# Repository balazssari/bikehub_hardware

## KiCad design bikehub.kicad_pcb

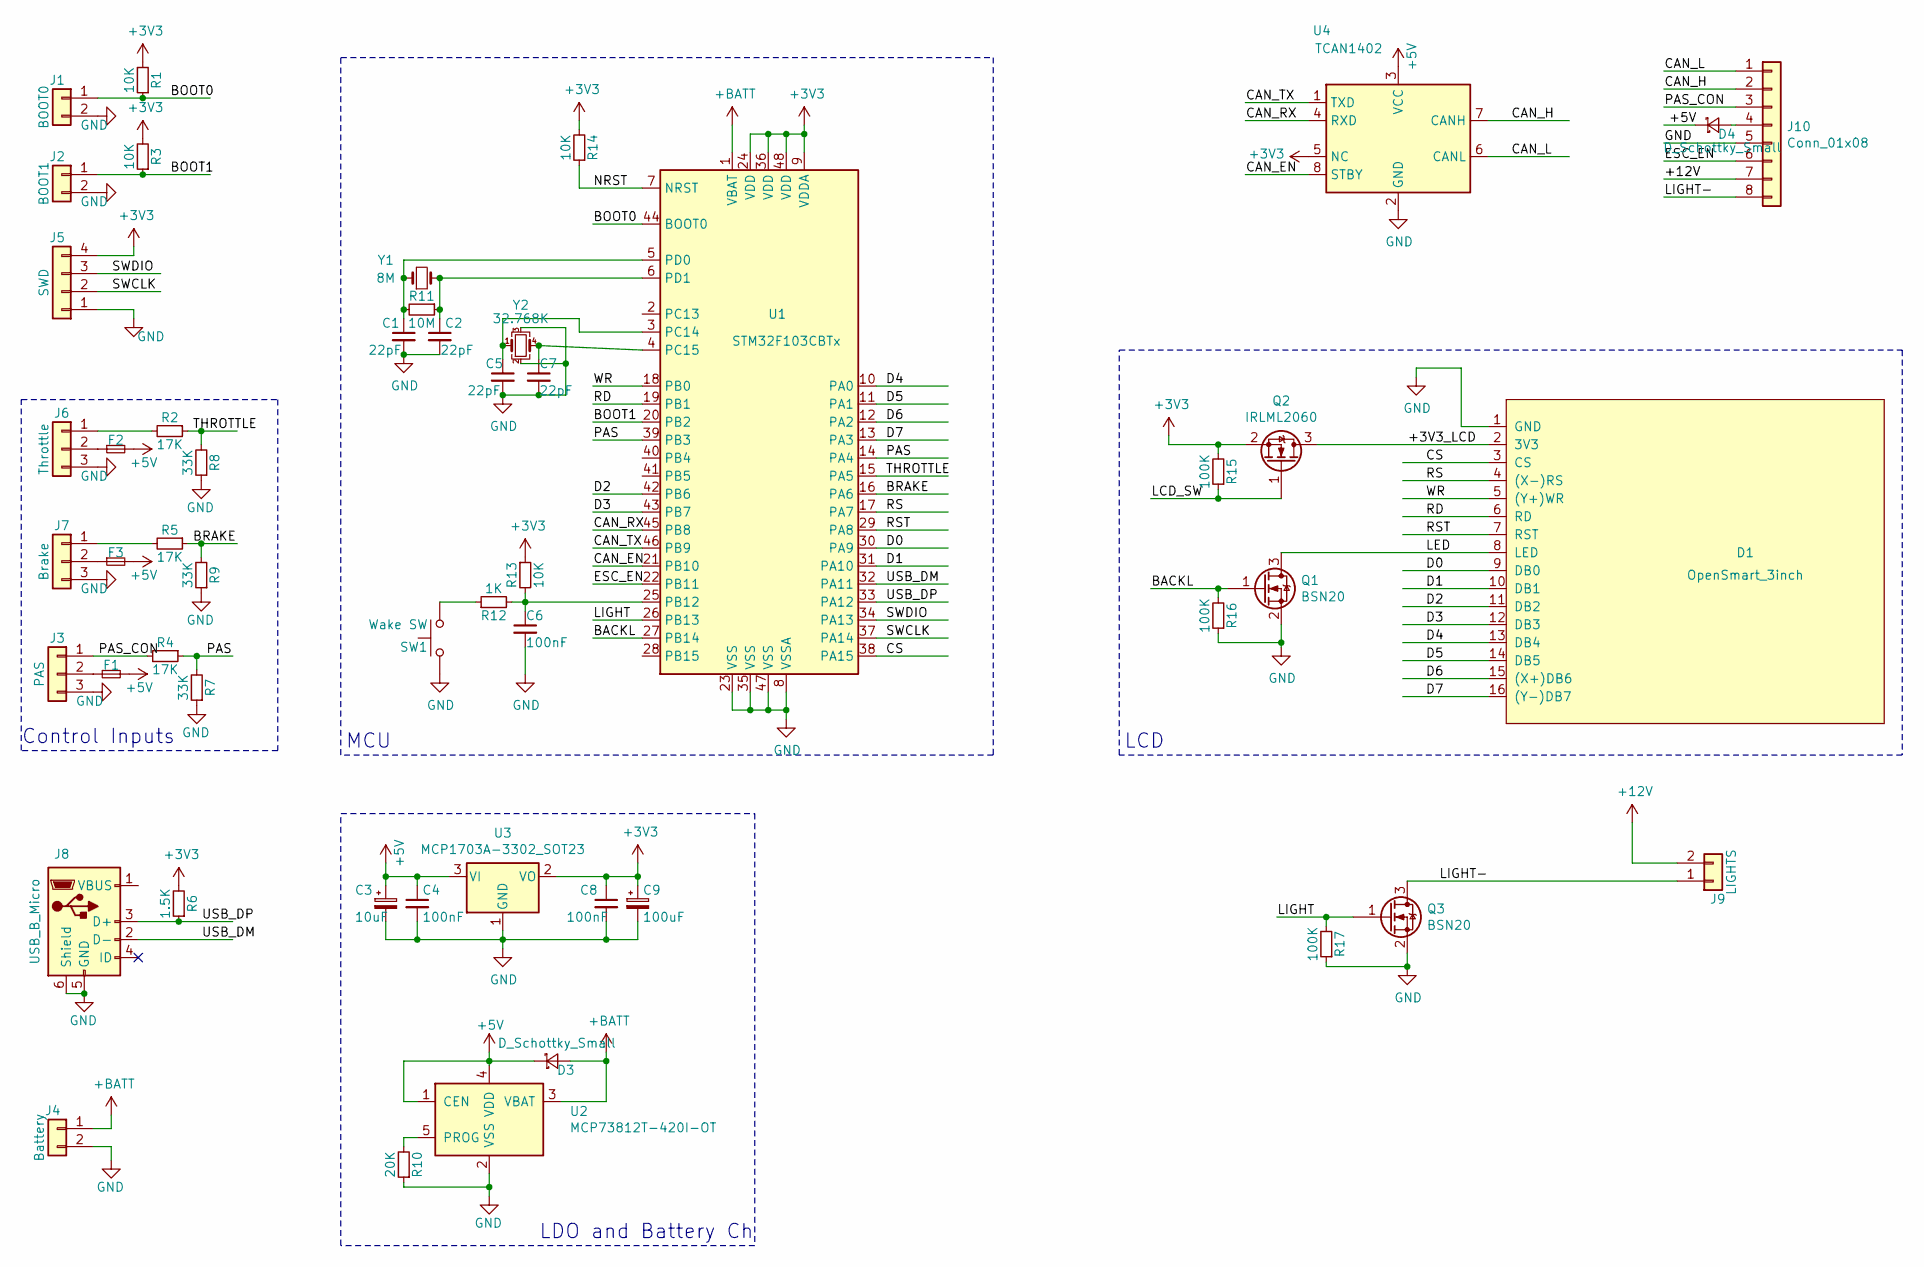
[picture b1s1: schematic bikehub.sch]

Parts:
C1, C2, C5, C7: 22pF; C_0805_2012Metric_Pad1.15x1.40mm_HandSolder
C3: 10uF; C_0805_2012Metric_Pad1.15x1.40mm_HandSolder
C4, C6, C8: 100nF; C_0805_2012Metric_Pad1.15x1.40mm_HandSolder
C9: 100uF; C_0805_2012Metric_Pad1.15x1.40mm_HandSolder
D1: OpenSmart_3inch; PinSocket_1x16_P2.54mm_Vertical_SMD_Pin1Left
D3, D4: D_Schottky_Small; D_SOD-123
F1, F2, F3: Fuse_Small; Fuse_0805_2012Metric
J1: BOOT0; SolderJumper-2_P1.3mm_Open_TrianglePad1.0x1.5mm
J2: BOOT1; SolderJumper-2_P1.3mm_Open_TrianglePad1.0x1.5mm
J3: PAS; JST_XH_S3B-XH-A_1x03_P2.50mm_Horizontal
J4: Battery; PinHeader_1x02_P2.54mm_Vertical
J5: SWD; PinHeader_1x04_P2.54mm_Horizontal
J6: Throttle; JST_XH_S3B-XH-A_1x03_P2.50mm_Horizontal
J7: Brake; JST_XH_S3B-XH-A_1x03_P2.50mm_Horizontal
J8: USB_B_Micro; USB_Micro-B_Molex_47346-0001
J9: LIGHTS; JST_XH_S2B-XH-A_1x02_P2.50mm_Horizontal
J10: Conn_01x08; JST_XH_S8B-XH-A_1x08_P2.50mm_Horizontal
Q1, Q3: BSN20; SOT-23
Q2: IRLML2060; SOT-23
R1, R3, R13, R14: 10K; R_0805_2012Metric_Pad1.15x1.40mm_HandSolder
R2, R4, R5: 17K; R_0805_2012Metric_Pad1.15x1.40mm_HandSolder
R6: 1.5K; R_0805_2012Metric_Pad1.15x1.40mm_HandSolder
R7, R8, R9: 33K; R_0805_2012Metric_Pad1.15x1.40mm_HandSolder
R10: 20K; R_0805_2012Metric_Pad1.15x1.40mm_HandSolder
R11: 10M; R_0805_2012Metric_Pad1.15x1.40mm_HandSolder
R12: 1K; R_0805_2012Metric_Pad1.15x1.40mm_HandSolder
R15, R16, R17: 100K; R_0805_2012Metric_Pad1.15x1.40mm_HandSolder
SW1: Wake SW; SW_SPST_EVQP7A
U1: STM32F103CBTx; LQFP-48_7x7mm_P0.5mm
U2: MCP73812T-420I-OT; SOT-23-5
U3: MCP1703A-3302_SOT23; SOT-23
U4: TCAN1402; SOIC-8_3.9x4.9mm_P1.27mm
Y1: 8M; Crystal_SMD_HC49-SD
Y2: 32.768K; Crystal_SMD_SeikoEpson_MC306-4Pin_8.0x3.2mm

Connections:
+3V3: C8.1, C9.1, J5.4, Q2.2 (S), R1.2, R3.2, R6.2, R13.1, R14.2, R15.2, U1.9 (VDDA), U1.24 (VDD), U1.36 (VDD), U1.48 (VDD), U3.2 (VO), U4.5 (NC)
+5V: C3.1, C4.1, D3.1 (K), D4.1 (K), F1.2, F2.2, F3.2, U2.1 (CEN), U2.4 (VDD), U3.3 (VI), U4.3 (VCC)
+12V: J9.2, J10.7
+BATT: D3.2 (A), J4.1, U1.1 (VBAT), U2.3 (VBAT)
/+3V3_LCD: D1.2 (3V3), Q2.3 (D)
/BACKL: Q1.1 (G), R16.2, U1.27 (PB14)
/BOOT0: J1.1, R1.1, U1.44 (BOOT0)
/BOOT1: J2.1, R3.1, U1.20 (PB2)
/BRAKE: R5.1, R9.2, U1.16 (PA6)
/CAN_EN: U1.21 (PB10), U4.8 (STBY)
/CAN_H: J10.2, U4.7 (CANH)
/CAN_L: J10.1, U4.6 (CANL)
/CAN_RX: U1.45 (PB8), U4.4 (RXD)
/CAN_TX: U1.46 (PB9), U4.1 (TXD)
/CS: D1.3 (CS), U1.38 (PA15)
/D0: D1.9 (DB0), U1.30 (PA9)
/D1: D1.10 (DB1), U1.31 (PA10)
/D2: D1.11 (DB2), U1.42 (PB6)
/D3: D1.12 (DB3), U1.43 (PB7)
/D4: D1.13 (DB4), U1.10 (PA0)
/D5: D1.14 (DB5), U1.11 (PA1)
/D6: D1.15 ((X+)DB6), U1.12 (PA2)
/D7: D1.16 ((Y-)DB7), U1.13 (PA3)
/ESC_EN: J10.6, U1.22 (PB11)
/LCD_SW: Q2.1 (G), R15.1
/LED: D1.8 (LED), Q1.3 (D)
/LIGHT: Q3.1 (G), R17.2, U1.26 (PB13)
/LIGHT-: J9.1, J10.8, Q3.3 (D)
/NRST: R14.1, U1.7 (NRST)
/PAS: R4.1, R7.2, U1.14 (PA4), U1.39 (PB3)
/PAS_CON: J3.1, J10.3, R4.2
/RD: D1.6 (RD), U1.19 (PB1)
/RS: D1.4 ((X-)RS), U1.17 (PA7)
/RST: D1.7 (RST), U1.29 (PA8)
/SWCLK: J5.2, U1.37 (PA14)
/SWDIO: J5.3, U1.34 (PA13)
/THROTTLE: R2.1, R8.2, U1.15 (PA5)
/USB_DM: J8.2 (D-), U1.32 (PA11)
/USB_DP: J8.3 (D+), R6.1, U1.33 (PA12)
/WR: D1.5 ((Y+)WR), U1.18 (PB0)
GND: C1.2, C2.2, C3.2, C4.2, C5.2, C6.2, C7.2, C8.2, C9.2, D1.1 (GND), J1.2, J2.2, J3.3, J4.2, J5.1, J6.3, J7.3, J8.5 (GND), J8.6 (Shield), J10.5, Q1.2 (S), Q3.2 (S), R7.1, R8.1, R9.1, R10.1, R16.1, R17.1, SW1.2, U1.8 (VSSA), U1.23 (VSS), U1.35 (VSS), U1.47 (VSS), U2.2 (VSS), U3.1 (GND), U4.2 (GND), Y2.2, Y2.3
unnamed: C1.1, R11.2, U1.5 (PD0), Y1.1
unnamed: C2.1, R11.1, U1.6 (PD1), Y1.2
unnamed: C5.1, U1.3 (PC14), Y2.1
unnamed: C6.1, R12.2, R13.2, U1.25 (PB12)
unnamed: C7.1, U1.4 (PC15), Y2.4
unnamed: D4.2 (A), J10.4
unnamed: F1.1, J3.2
unnamed: F2.1, J6.2
unnamed: F3.1, J7.2
unnamed: J6.1, R2.2
unnamed: J7.1, R5.2
unnamed: R10.2, U2.5 (PROG)
unnamed: R12.1, SW1.1

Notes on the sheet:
LDO and Battery Ch
Control Inputs
LCD
MCU

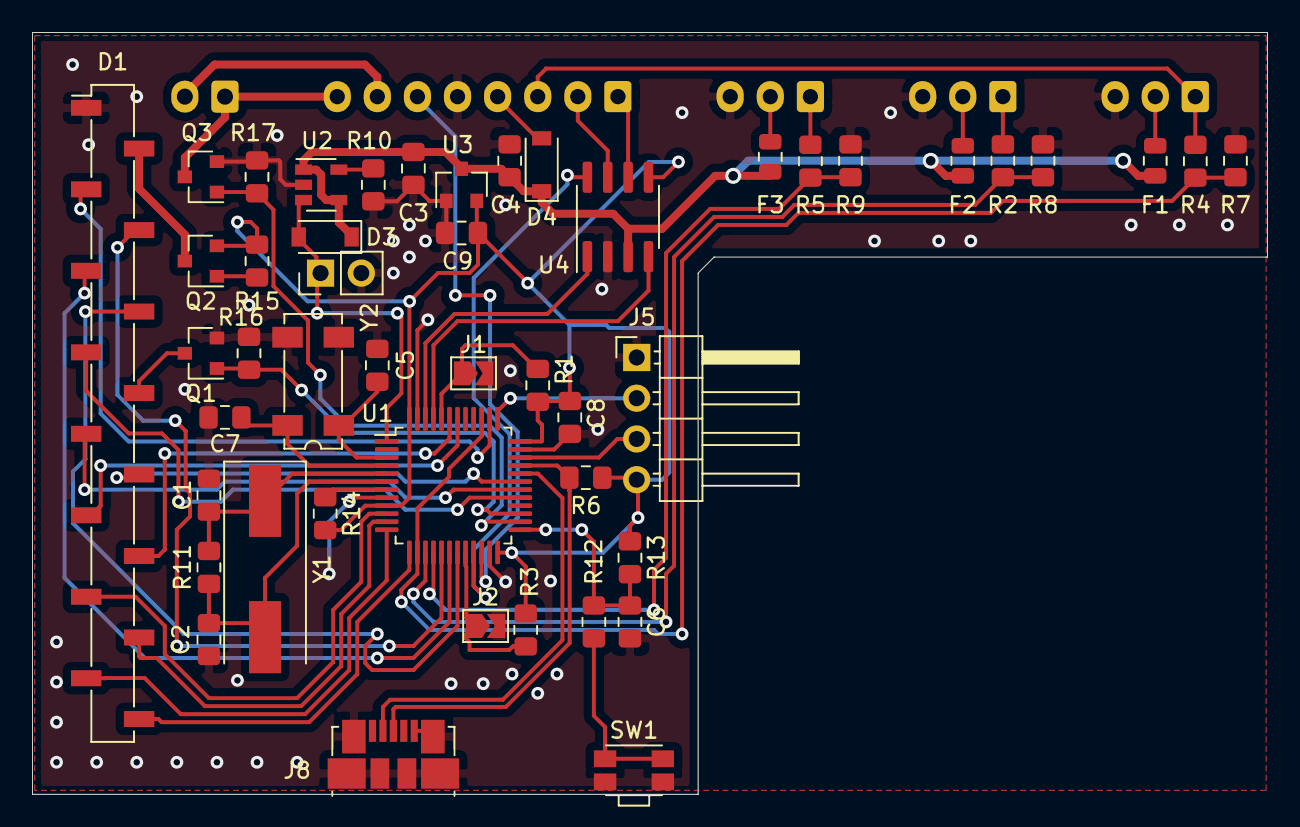
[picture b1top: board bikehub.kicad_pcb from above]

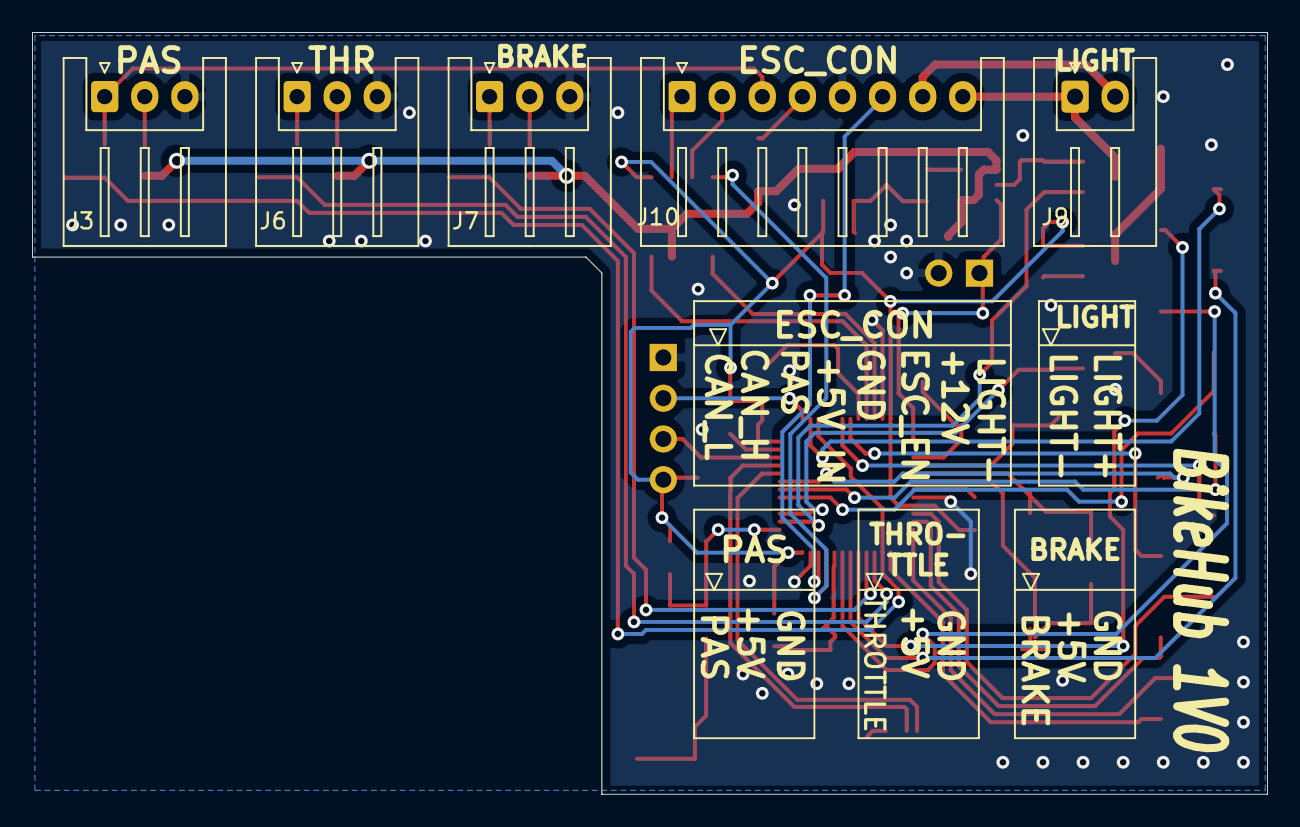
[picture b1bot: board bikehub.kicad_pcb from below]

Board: 2 copper layers, 77.0 x 47.5 mm, 52 parts (5 on the bottom side), 54 nets.
